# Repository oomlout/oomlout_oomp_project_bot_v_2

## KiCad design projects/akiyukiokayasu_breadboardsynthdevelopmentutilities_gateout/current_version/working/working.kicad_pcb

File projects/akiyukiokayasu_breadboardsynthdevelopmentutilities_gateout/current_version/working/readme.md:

# breadboardsynthdevelopmentutilities
 
## summary 
* id: akiyukiokayasu_breadboardsynthdevelopmentutilities_gateout
* user: akiyukiokayasu
* name: breadboardsynthdevelopmentutilities
* board: gateout
* repo: https://github.com/AkiyukiOkayasu/BreadBoardSynthDevelopmentUtilities
* src_file_repo_kicad_pcb: GateOut/GateOut.kicad_pcb
* src_file_repo_kicad_pcb_link: https://github.com/AkiyukiOkayasu/BreadBoardSynthDevelopmentUtilities/tree/main/GateOut/GateOut.kicad_pcb
* src_file_repo_kicad_sch: GateOut/GateOut.kicad_sch
* src_file_repo_kicad_sch_link: https://github.com/AkiyukiOkayasu/BreadBoardSynthDevelopmentUtilities/tree/main/GateOut/GateOut.kicad_sch

* src_file_repo_sch: 
* src_file_repo_sch_link: https://github.com/AkiyukiOkayasu/BreadBoardSynthDevelopmentUtilities/tree/main/
* full details link: https://github.com/oomlout/oomlout_oomp_project_bot_v_2/tree/main/projects/akiyukiokayasu_breadboardsynthdevelopmentutilities_gateout/current_version/working  

## schematic  
  
[schematic (pdf)](working_schematic.pdf) 

## pcb  

[board (pdf)](working.pdf)  

## working_bom
| Id | Designator | Footprint | Quantity | Designation | Supplier and ref |  | None | 
| --- | --- | --- | --- | --- | --- | --- | --- | 
| 1 | R6,R4 | R_0402_1005Metric_Pad0.72x0.64mm_HandSolder | 2 | 10k |  |  | [''] | 
| 2 | U1 | SOIC-8_3.9x4.9mm_P1.27mm | 1 | LM358 |  |  | [''] | 
| 3 | R5,R3 | R_0402_1005Metric_Pad0.72x0.64mm_HandSolder | 2 | 39k |  |  | [''] | 
| 4 | R7,R8 | R_0402_1005Metric_Pad0.72x0.64mm_HandSolder | 2 | 56k |  |  | [''] | 
| 5 | D1,D2 | LED_0402_1005Metric_Pad0.77x0.64mm_HandSolder | 2 | LED |  |  | [''] | 
| 6 | R9,R1,R2,R10 | R_0402_1005Metric_Pad0.72x0.64mm_HandSolder | 4 | 1k |  |  | [''] | 
| 7 | C1 | C_0402_1005Metric_Pad0.74x0.62mm_HandSolder | 1 | 0.1u |  |  | [''] | 
| 8 | J2,J1 | PinHeader_1x04_P2.54mm_Vertical | 2 | Conn_01x04 |  |  | [''] | 

## bom_schematic
| Ref | Qnty | Value | Cmp name | Footprint | Description | Vendor | DNP | 
| --- | --- | --- | --- | --- | --- | --- | --- | 
| C1 | 1 | 0.1u | C_Small | Capacitor_SMD:C_0402_1005Metric_Pad0.74x0.62mm_HandSolder | Unpolarized capacitor, small symbol |  |  | 
| D1, D2 | 2 | LED | LED | LED_SMD:LED_0402_1005Metric_Pad0.77x0.64mm_HandSolder | Light emitting diode |  |  | 
| J1, J2 | 2 | Conn_01x04 | Conn_01x04 | Connector_PinHeader_2.54mm:PinHeader_1x04_P2.54mm_Vertical | Generic connector, single row, 01x04, script generated (kicad-library-utils/schlib/autogen/connector/) |  |  | 
| R1, R2, R9, R10 | 4 | 1k | R | Resistor_SMD:R_0402_1005Metric_Pad0.72x0.64mm_HandSolder | Resistor |  |  | 
| R3, R5 | 2 | 39k | R | Resistor_SMD:R_0402_1005Metric_Pad0.72x0.64mm_HandSolder | Resistor |  |  | 
| R4, R6 | 2 | 10k | R | Resistor_SMD:R_0402_1005Metric_Pad0.72x0.64mm_HandSolder | Resistor |  |  | 
| R7, R8 | 2 | 56k | R | Resistor_SMD:R_0402_1005Metric_Pad0.72x0.64mm_HandSolder | Resistor |  |  | 
| U1 | 1 | LM358 | LM358 | Package_SO:SOIC-8_3.9x4.9mm_P1.27mm | Low-Power, Dual Operational Amplifiers, DIP-8/SOIC-8/TO-99-8 |  |  |

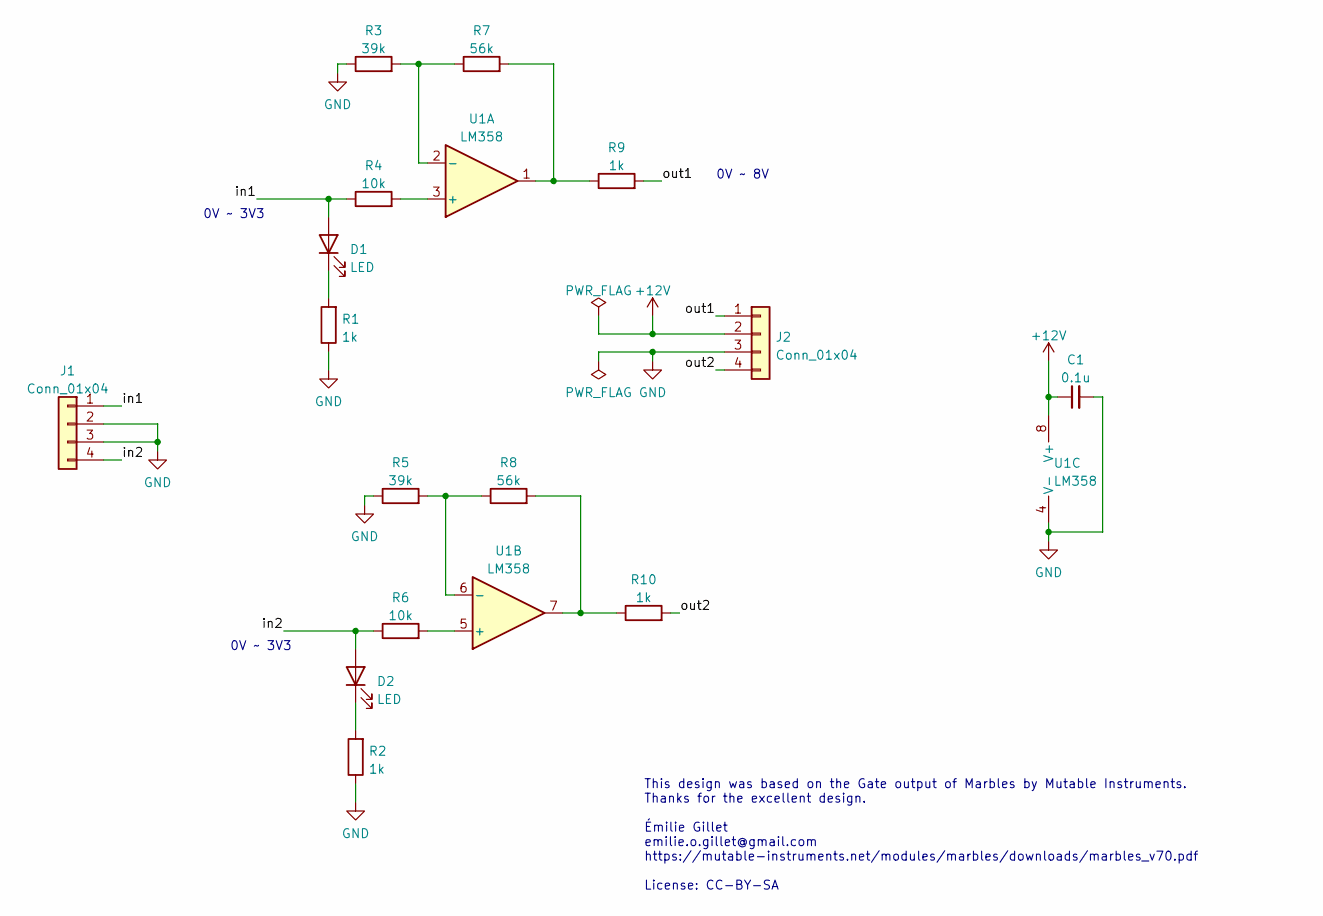
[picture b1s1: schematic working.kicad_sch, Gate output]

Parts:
C1: 0.1u; C_0402_1005Metric_Pad0.74x0.62mm_HandSolder
D1, D2: LED; LED_0402_1005Metric_Pad0.77x0.64mm_HandSolder
J1, J2: Conn_01x04; PinHeader_1x04_P2.54mm_Vertical
R1, R2, R9, R10: 1k; R_0402_1005Metric_Pad0.72x0.64mm_HandSolder
R3, R5: 39k; R_0402_1005Metric_Pad0.72x0.64mm_HandSolder
R4, R6: 10k; R_0402_1005Metric_Pad0.72x0.64mm_HandSolder
R7, R8: 56k; R_0402_1005Metric_Pad0.72x0.64mm_HandSolder
U1: LM358; SOIC-8_3.9x4.9mm_P1.27mm

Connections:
+12V: C1.1, J2.2, U1.8 (V+)
/in1: D1.2 (A), J1.1, R4.1
/in2: D2.2 (A), J1.4, R6.1
/out1: J2.1, R9.2
/out2: J2.4, R10.2
GND: C1.2, J1.2, J1.3, J2.3, R1.1, R2.1, R3.1, R5.1, U1.4 (V-)
unnamed: D1.1 (K), R1.2
unnamed: D2.1 (K), R2.2
unnamed: R3.2, R7.1, U1.2 (-)
unnamed: R4.2, U1.3 (+)
unnamed: R5.2, R8.1, U1.6 (-)
unnamed: R6.2, U1.5 (+)
unnamed: R7.2, R9.1, U1.1
unnamed: R8.2, R10.1, U1.7

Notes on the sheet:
0V ~ 3V3
This design was based on the Gate output of Marbles by Mutable Instruments. Thanks for the excellent design. Émilie Gillet emilie.o.gillet@gmail.com https://mutable-instruments.net/modules/marbles/downloads/marbles_v70.pdf License: CC-BY-SA
0V ~ 8V

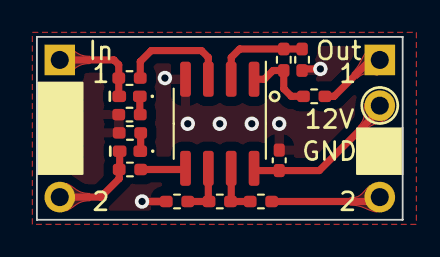
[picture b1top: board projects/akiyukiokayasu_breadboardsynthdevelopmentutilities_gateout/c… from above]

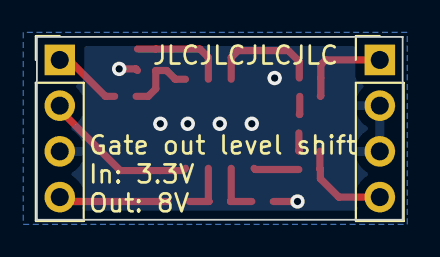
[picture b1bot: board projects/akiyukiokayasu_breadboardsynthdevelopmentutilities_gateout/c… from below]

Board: 2 copper layers, 20.3 x 10.2 mm, 16 parts (2 on the bottom side), 14 nets.

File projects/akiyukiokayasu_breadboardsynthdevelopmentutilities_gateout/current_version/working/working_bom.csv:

"Id";"Designator";"Footprint";"Quantity";"Designation";"Supplier and ref";
1;"R6,R4";"R_0402_1005Metric_Pad0.72x0.64mm_HandSolder";2;"10k";;;
2;"U1";"SOIC-8_3.9x4.9mm_P1.27mm";1;"LM358";;;
3;"R5,R3";"R_0402_1005Metric_Pad0.72x0.64mm_HandSolder";2;"39k";;;
4;"R7,R8";"R_0402_1005Metric_Pad0.72x0.64mm_HandSolder";2;"56k";;;
5;"D1,D2";"LED_0402_1005Metric_Pad0.77x0.64mm_HandSolder";2;"LED";;;
6;"R9,R1,R2,R10";"R_0402_1005Metric_Pad0.72x0.64mm_HandSolder";4;"1k";;;
7;"C1";"C_0402_1005Metric_Pad0.74x0.62mm_HandSolder";1;"0.1u";;;
8;"J2,J1";"PinHeader_1x04_P2.54mm_Vertical";2;"Conn_01x04";;;

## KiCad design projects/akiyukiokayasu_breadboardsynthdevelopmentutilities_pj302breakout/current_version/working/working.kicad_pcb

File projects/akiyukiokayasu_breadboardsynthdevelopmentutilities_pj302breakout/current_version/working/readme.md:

# breadboardsynthdevelopmentutilities
 
## summary 
* id: akiyukiokayasu_breadboardsynthdevelopmentutilities_pj302breakout
* user: akiyukiokayasu
* name: breadboardsynthdevelopmentutilities
* board: pj302breakout
* repo: https://github.com/AkiyukiOkayasu/BreadBoardSynthDevelopmentUtilities
* src_file_repo_kicad_pcb: PJ302Breakout/PJ302Breakout.kicad_pcb
* src_file_repo_kicad_pcb_link: https://github.com/AkiyukiOkayasu/BreadBoardSynthDevelopmentUtilities/tree/main/PJ302Breakout/PJ302Breakout.kicad_pcb
* src_file_repo_kicad_sch: PJ302Breakout/PJ302Breakout.kicad_sch
* src_file_repo_kicad_sch_link: https://github.com/AkiyukiOkayasu/BreadBoardSynthDevelopmentUtilities/tree/main/PJ302Breakout/PJ302Breakout.kicad_sch

* src_file_repo_sch: 
* src_file_repo_sch_link: https://github.com/AkiyukiOkayasu/BreadBoardSynthDevelopmentUtilities/tree/main/
* full details link: https://github.com/oomlout/oomlout_oomp_project_bot_v_2/tree/main/projects/akiyukiokayasu_breadboardsynthdevelopmentutilities_pj302breakout/current_version/working  

## schematic  
  
[schematic (pdf)](working_schematic.pdf) 

## pcb  

[board (pdf)](working.pdf)  

## working_bom
| Id | Designator | Footprint | Quantity | Designation | Supplier and ref |  | None | 
| --- | --- | --- | --- | --- | --- | --- | --- | 
| 1 | J1 | PJ302M | 1 | PJ302M |  |  | [''] | 
| 2 | J3 | PinHeader_1x02_P2.54mm_Vertical | 1 | Conn_01x02 |  |  | [''] | 
| 3 | J2 | PinHeader_1x04_P2.54mm_Vertical | 1 | Conn_01x04 |  |  | [''] | 

## bom_schematic
| Ref | Qnty | Value | Cmp name | Footprint | Description | Vendor | DNP | 
| --- | --- | --- | --- | --- | --- | --- | --- | 
| J1 | 1 | PJ302M | PJ302M | Akiyuki_Footprint:PJ302M | 2-pin audio jack receptable (mono/TS connector) with switching contact |  |  | 
| J2 | 1 | Conn_01x04 | Conn_01x04 | Connector_PinHeader_2.54mm:PinHeader_1x04_P2.54mm_Vertical | Generic connector, single row, 01x04, script generated (kicad-library-utils/schlib/autogen/connector/) |  |  | 
| J3 | 1 | Conn_01x02 | Conn_01x02 | Connector_PinHeader_2.54mm:PinHeader_1x02_P2.54mm_Vertical | Generic connector, single row, 01x02, script generated (kicad-library-utils/schlib/autogen/connector/) |  |  |

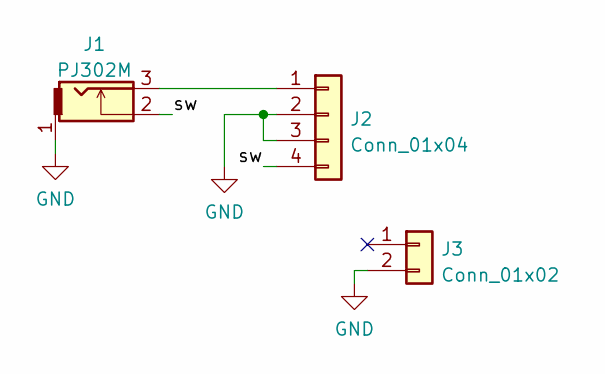
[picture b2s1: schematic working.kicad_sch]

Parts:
J1: PJ302M
J2: Conn_01x04; PinHeader_1x04_P2.54mm_Vertical
J3: Conn_01x02; PinHeader_1x02_P2.54mm_Vertical

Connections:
/sw: J1.2, J2.4
GND: J1.1, J2.2, J2.3, J3.2
unnamed: J1.3, J2.1

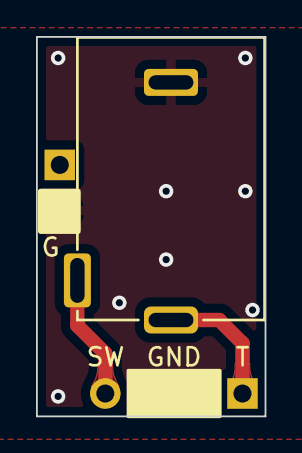
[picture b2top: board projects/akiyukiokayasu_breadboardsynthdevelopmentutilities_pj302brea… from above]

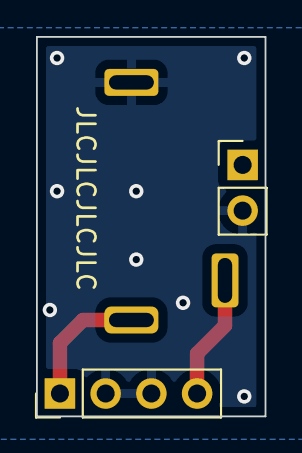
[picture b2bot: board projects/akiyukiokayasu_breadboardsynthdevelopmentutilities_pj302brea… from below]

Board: 2 copper layers, 12.7 x 21.1 mm, 3 parts (2 on the bottom side), 3 nets.

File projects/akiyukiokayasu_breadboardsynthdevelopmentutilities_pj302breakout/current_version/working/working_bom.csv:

"Id";"Designator";"Footprint";"Quantity";"Designation";"Supplier and ref";
1;"J1";"PJ302M";1;"PJ302M";;;
2;"J3";"PinHeader_1x02_P2.54mm_Vertical";1;"Conn_01x02";;;
3;"J2";"PinHeader_1x04_P2.54mm_Vertical";1;"Conn_01x04";;;

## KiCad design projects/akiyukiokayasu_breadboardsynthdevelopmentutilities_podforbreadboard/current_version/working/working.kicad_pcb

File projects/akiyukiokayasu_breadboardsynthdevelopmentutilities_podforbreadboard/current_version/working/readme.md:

# breadboardsynthdevelopmentutilities
 
## summary 
* id: akiyukiokayasu_breadboardsynthdevelopmentutilities_podforbreadboard
* user: akiyukiokayasu
* name: breadboardsynthdevelopmentutilities
* board: podforbreadboard
* repo: https://github.com/AkiyukiOkayasu/BreadBoardSynthDevelopmentUtilities
* src_file_repo_kicad_pcb: PodForBreadboard/PodForBreadboard.kicad_pcb
* src_file_repo_kicad_pcb_link: https://github.com/AkiyukiOkayasu/BreadBoardSynthDevelopmentUtilities/tree/main/PodForBreadboard/PodForBreadboard.kicad_pcb
* src_file_repo_kicad_sch: PodForBreadboard/PodForBreadboard.kicad_sch
* src_file_repo_kicad_sch_link: https://github.com/AkiyukiOkayasu/BreadBoardSynthDevelopmentUtilities/tree/main/PodForBreadboard/PodForBreadboard.kicad_sch

* src_file_repo_sch: 
* src_file_repo_sch_link: https://github.com/AkiyukiOkayasu/BreadBoardSynthDevelopmentUtilities/tree/main/
* full details link: https://github.com/oomlout/oomlout_oomp_project_bot_v_2/tree/main/projects/akiyukiokayasu_breadboardsynthdevelopmentutilities_podforbreadboard/current_version/working  

## schematic  
  
[schematic (pdf)](working_schematic.pdf) 

## pcb  

[board (pdf)](working.pdf)  

## working_bom
| Id | Designator | Footprint | Quantity | Designation | Supplier and ref |  | None | 
| --- | --- | --- | --- | --- | --- | --- | --- | 
| 1 | RV1 | ALPS_RK09D117000B | 1 | ALPS_RK09D |  |  | [''] | 
| 2 | J1 | PinHeader_2x02_P2.54mm_Vertical | 1 | Conn_02x02_Odd_Even |  |  | [''] | 
| 3 | J2 | PinHeader_1x04_P2.54mm_Vertical | 1 | Conn_01x04 |  |  | [''] | 

## bom_schematic
| Ref | Qnty | Value | Cmp name | Footprint | Description | Vendor | DNP | 
| --- | --- | --- | --- | --- | --- | --- | --- | 
| J1 | 1 | Conn_02x02_Odd_Even | Conn_02x02_Odd_Even | Connector_PinHeader_2.54mm:PinHeader_2x02_P2.54mm_Vertical | Generic connector, double row, 02x02, odd/even pin numbering scheme (row 1 odd numbers, row 2 even numbers), script generated (kicad-library-utils/schlib/autogen/connector/) |  |  | 
| J2 | 1 | Conn_01x04 | Conn_01x04 | Connector_PinHeader_2.54mm:PinHeader_1x04_P2.54mm_Vertical | Generic connector, single row, 01x04, script generated (kicad-library-utils/schlib/autogen/connector/) |  |  | 
| RV1 | 1 | ALPS_RK09D | ALPS_RK09D | Akiyuki_Footprint:ALPS_RK09D117000B | Pot |  |  |

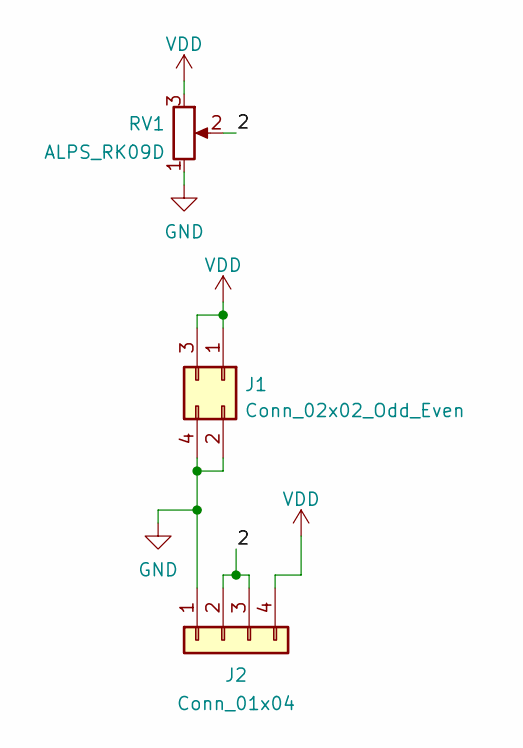
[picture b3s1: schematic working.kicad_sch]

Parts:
J1: Conn_02x02_Odd_Even; PinHeader_2x02_P2.54mm_Vertical
J2: Conn_01x04; PinHeader_1x04_P2.54mm_Vertical
RV1: ALPS_RK09D; ALPS_RK09D117000B

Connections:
/2: J2.2, J2.3, RV1.2
GND: J1.2, J1.4, J2.1, RV1.1
VDD: J1.1, J1.3, J2.4, RV1.3

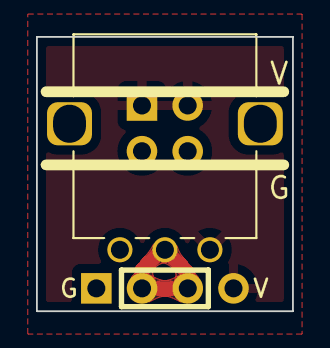
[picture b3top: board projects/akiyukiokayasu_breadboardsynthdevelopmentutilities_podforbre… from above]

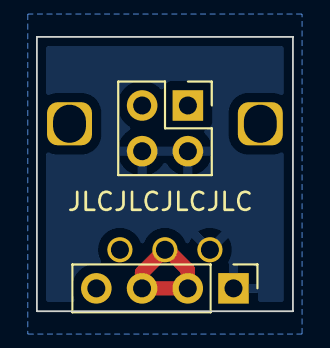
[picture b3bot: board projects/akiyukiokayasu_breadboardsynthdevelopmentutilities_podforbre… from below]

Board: 2 copper layers, 14.2 x 15.2 mm, 3 parts (2 on the bottom side), 3 nets.

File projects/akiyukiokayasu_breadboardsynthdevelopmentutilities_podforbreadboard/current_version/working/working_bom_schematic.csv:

"Source:","C:\gh\oomlout_oomp_project_bot_v_2\projects\akiyukiokayasu_breadboardsynthdevelopmentutilities_podforbreadboard\current_version\working\working.kicad_sch"
"Date:","11/09/2023 22:35:03"
"Tool:","Eeschema 7.0.6"
"Generator:","C:/Program Files/KiCad/7.0/bin/scripting/plugins/bom_csv_grouped_by_value_with_fp.py"
"Component Count:","3"
"Ref","Qnty","Value","Cmp name","Footprint","Description","Vendor","DNP"
"J1","1","Conn_02x02_Odd_Even","Conn_02x02_Odd_Even","Connector_PinHeader_2.54mm:PinHeader_2x02_P2.54mm_Vertical","Generic connector, double row, 02x02, odd/even pin numbering scheme (row 1 odd numbers, row 2 even numbers), script generated (kicad-library-utils/schlib/autogen/connector/)","",""
"J2","1","Conn_01x04","Conn_01x04","Connector_PinHeader_2.54mm:PinHeader_1x04_P2.54mm_Vertical","Generic connector, single row, 01x04, script generated (kicad-library-utils/schlib/autogen/connector/)","",""
"RV1","1","ALPS_RK09D","ALPS_RK09D","Akiyuki_Footprint:ALPS_RK09D117000B","Pot","",""

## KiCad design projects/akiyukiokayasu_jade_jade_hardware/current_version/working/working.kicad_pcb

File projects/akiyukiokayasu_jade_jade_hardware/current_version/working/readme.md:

# jade
 
## summary 
* id: akiyukiokayasu_jade_jade_hardware
* user: akiyukiokayasu
* name: jade
* board: jade_hardware
* repo: https://github.com/AkiyukiOkayasu/jade
* src_file_repo_kicad_pcb: Hardware/jade_hardware.kicad_pcb
* src_file_repo_kicad_pcb_link: https://github.com/AkiyukiOkayasu/jade/tree/main/Hardware/jade_hardware.kicad_pcb
* src_file_repo_kicad_sch: Hardware/jade_hardware.kicad_sch
* src_file_repo_kicad_sch_link: https://github.com/AkiyukiOkayasu/jade/tree/main/Hardware/jade_hardware.kicad_sch

* src_file_repo_sch: 
* src_file_repo_sch_link: https://github.com/AkiyukiOkayasu/jade/tree/main/
* full details link: https://github.com/oomlout/oomlout_oomp_project_bot_v_2/tree/main/projects/akiyukiokayasu_jade_jade_hardware/current_version/working  

## schematic  
  
[schematic (pdf)](working_schematic.pdf) 

## pcb  

[board (pdf)](working.pdf)  

## working_bom
| Id | Designator | Footprint | Quantity | Designation | Supplier and ref |  | None | 
| --- | --- | --- | --- | --- | --- | --- | --- | 
| 1 | C1 | C_0805_2012Metric_Pad1.18x1.45mm_HandSolder | 1 | 10u |  |  | [''] | 
| 2 | C2 | C_0603_1608Metric_Pad1.08x0.95mm_HandSolder | 1 | 0.1u |  |  | [''] | 
| 3 | D1,D2,D3,D4 | D_SOD-123 | 4 | 1N4148W |  |  | [''] | 
| 4 | D5 | D_SOD-123 | 1 | 1N5819HW |  |  | [''] | 
| 5 | J1,J2,J3,J4,J7,J8 | PJ302M | 6 | PJ302M |  |  | [''] | 
| 6 | J5 | PinHeader_2x05_P2.54mm_Horizontal | 1 | Conn_02x05_Odd_Even |  |  | [''] | 
| 7 | J6 | PinHeader_2x03_P2.54mm_Horizontal | 1 | Conn_02x03_Odd_Even |  |  | [''] | 
| 8 | R1,R3,R4,R5,R6,R8,R2,R7 | R_0603_1608Metric_Pad0.98x0.95mm_HandSolder | 8 | 100k |  |  | [''] | 
| 9 | R9,R10 | R_0603_1608Metric_Pad0.98x0.95mm_HandSolder | 2 | 39k |  |  | [''] | 
| 10 | R13,R14 | R_0603_1608Metric_Pad0.98x0.95mm_HandSolder | 2 | 56k |  |  | [''] | 
| 11 | R15,R16 | R_0603_1608Metric_Pad0.98x0.95mm_HandSolder | 2 | 1k |  |  | [''] | 
| 12 | U2 | SOP-8_3.9x4.9mm_P1.27mm | 1 | LM358 |  |  | [''] | 
| 13 | Q4,Q3,Q2,Q1 | SOT-23 | 4 | MMBT3904 |  |  | [''] | 
| 14 | U1 | Seeeduino_XIAO_NonBottomPad | 1 | SeeeduinoXIAO |  |  | [''] | 
| 15 | R12,R11 | R_0603_1608Metric_Pad0.98x0.95mm_HandSolder | 2 | 47k |  |  | [''] | 

## bom_schematic
| Ref | Qnty | Value | Cmp name | Footprint | Description | Vendor | DNP | 
| --- | --- | --- | --- | --- | --- | --- | --- | 
| C1, C2 | 2 | 10u | C_Small | Capacitor_SMD:C_0805_2012Metric_Pad1.18x1.45mm_HandSolder | Unpolarized capacitor, small symbol |  |  | 
| C3, C4 | 2 | 0.1u | C_Small | Capacitor_SMD:C_0402_1005Metric_Pad0.74x0.62mm_HandSolder | Unpolarized capacitor, small symbol |  |  | 
| D1, D2, D3, D4 | 4 | 1N4148W | D_Small | Diode_SMD:D_SOD-123 | Diode, small symbol |  |  | 
| D5 | 1 | 1N5819HW | D_Small | Diode_SMD:D_SOD-123 | Diode, small symbol |  |  | 
| J1, J2, J3, J4, J6, J7 | 6 | PJ302M | PJ302M | Akiyuki_Footprint:PJ302M | 2-pin audio jack receptable (mono/TS connector) with switching contact |  |  | 
| J5 | 1 | Conn_02x05_Odd_Even | Conn_02x05_Odd_Even | Connector_PinHeader_2.54mm:PinHeader_2x05_P2.54mm_Horizontal | Generic connector, double row, 02x05, odd/even pin numbering scheme (row 1 odd numbers, row 2 even numbers), script generated (kicad-library-utils/schlib/autogen/connector/) |  |  | 
| J8 | 1 | monome ii | Conn_02x03_Odd_Even | Connector_PinHeader_2.54mm:PinHeader_2x03_P2.54mm_Horizontal | Generic connector, double row, 02x03, odd/even pin numbering scheme (row 1 odd numbers, row 2 even numbers), script generated (kicad-library-utils/schlib/autogen/connector/) |  |  | 
| Q1 | 1 | DTC114E | DTC114E |  | Digital NPN Transistor, 10k/10k, SOT-23 |  |  | 
| R1, R2, R3, R4 | 4 | 100k | R_Small | Resistor_SMD:R_0402_1005Metric_Pad0.72x0.64mm_HandSolder | Resistor, small symbol |  |  | 
| R5, R6 | 2 | 47k | R_Small | Resistor_SMD:R_0402_1005Metric_Pad0.72x0.64mm_HandSolder | Resistor, small symbol |  |  | 
| R7, R8 | 2 | 2k2 | R_Small | Resistor_SMD:R_0402_1005Metric_Pad0.72x0.64mm_HandSolder | Resistor, small symbol |  |  | 
| SW1 | 1 | SW_DIP_x02 | SW_DIP_x02 | Akiyuki_Footprint:OTAX_KHS_2 | 2x DIP Switch, Single Pole Single Throw (SPST) switch, small symbol |  |  | 
| U1 | 1 | TLP293-4 | TLP291-4 | Package_SO:SOIC-16_4.55x10.3mm_P1.27mm | Quad DC Optocoupler, Vce 80V, CTR 50-100%, SOP16 |  |  | 
| U2 | 1 | SeeeduinoXIAO | SeeeduinoXIAO_NonBottomPad | Akiyuki_Footprint:Seeeduino_XIAO_NonBottomPad |  |  |  | 
| U3 | 1 | MIC39100 | MIC39100 | Package_TO_SOT_SMD:SOT-223-3_TabPin2 | Linear Voltage Regulator IC 1 Output 1A SOT-223-3 |  |  | 
| U4, U5 | 2 | TLP291 | TLP291 | Package_SO:SOIC-4_4.55x2.6mm_P1.27mm | DC Optocoupler, Vce 80V, CTR 50-100%, SOP4 |  |  | 
| U6 | 1 | ADuM1250 | ADuM1250 | Package_SO:SOIC-8_3.9x4.9mm_P1.27mm | I2C isolator |  |  |

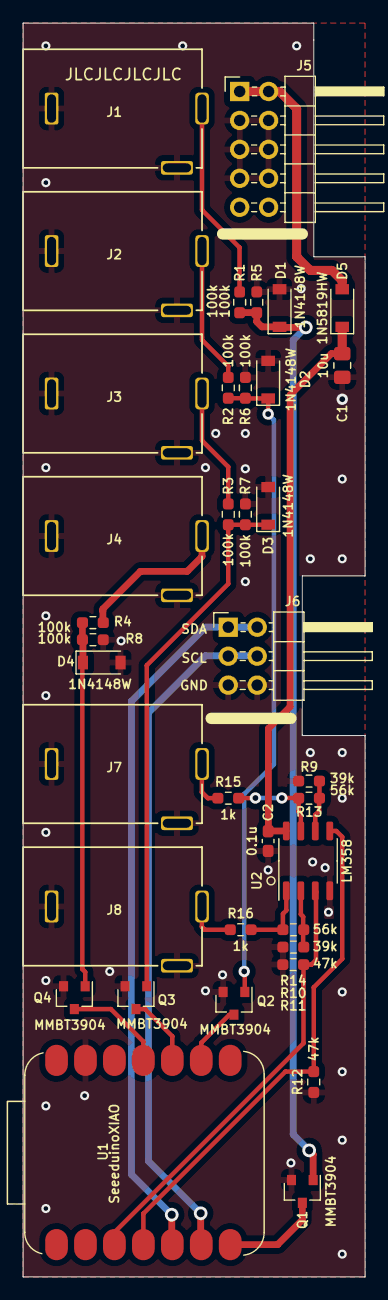
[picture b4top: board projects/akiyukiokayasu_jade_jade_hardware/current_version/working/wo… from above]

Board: 2 copper layers, 30.0 x 110.0 mm, 37 parts (0 on the bottom side), 25 nets.

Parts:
C1: 10u; C_0805_2012Metric_Pad1.18x1.45mm_HandSolder
C2: 0.1u; C_0603_1608Metric_Pad1.08x0.95mm_HandSolder
D1, D2, D3, D4: 1N4148W; D_SOD-123
D5: 1N5819HW; D_SOD-123
J1, J2, J3, J4, J7, J8: PJ302M
J5: Conn_02x05_Odd_Even; PinHeader_2x05_P2.54mm_Horizontal
J6: Conn_02x03_Odd_Even; PinHeader_2x03_P2.54mm_Horizontal
Q1, Q2, Q3, Q4: MMBT3904; SOT-23
R1, R2, R3, R4, R5, R6, R7, R8: 100k; R_0603_1608Metric_Pad0.98x0.95mm_HandSolder
R9, R10: 39k; R_0603_1608Metric_Pad0.98x0.95mm_HandSolder
R11, R12: 47k; R_0603_1608Metric_Pad0.98x0.95mm_HandSolder
R13, R14: 56k; R_0603_1608Metric_Pad0.98x0.95mm_HandSolder
R15, R16: 1k; R_0603_1608Metric_Pad0.98x0.95mm_HandSolder
U1: SeeeduinoXIAO; Seeeduino_XIAO_NonBottomPad
U2: LM358; SOP-8_3.9x4.9mm_P1.27mm

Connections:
+12V: C1.1, C2.1, D5.1, U2.8
/CLOCK_OUT: R11.2, U1.3, U2.3
/GATE_IN1: Q1.3, U1.7
/GATE_IN2: Q2.3, U1.9
/GATE_IN3: Q3.3, U1.10
/GATE_IN4: Q4.3, U1.11
/GATE_OUT: R12.2, U1.4, U2.5
/SCL: J6.3, J6.4, U1.6
/SDA: J6.1, J6.2, U1.5
GND: C1.2, C2.2, D1.2, D2.2, D3.2, D4.2, J1.1, J1.2, J2.1, J2.2, J3.1, J3.2, J4.1, J4.2, J5.3, J5.4, J5.5, J5.6, J5.7, J5.8, J6.5, J6.6, J7.1, J7.2, J8.1, J8.2, Q1.2, Q2.2, Q3.2, Q4.2, R5.1, R6.1, R7.1, R8.1, R9.2, R10.2, R11.1, R12.1, U1.13, U2.4
unnamed: D1.1, Q1.1, R1.1, R5.2
unnamed: D2.1, Q2.1, R2.1, R6.2
unnamed: D3.1, Q3.1, R3.1, R7.2
unnamed: D4.1, Q4.1, R4.1, R8.2
unnamed: D5.2, J5.1, J5.2
unnamed: J1.3, R1.2
unnamed: J2.3, R2.2
unnamed: J3.3, R3.2
unnamed: J4.3, R4.2
unnamed: J7.3, R15.1
unnamed: J8.3, R16.1
unnamed: R10.1, R14.2, U2.2
unnamed: R13.1, R15.2, U2.7
unnamed: R9.1, R13.2, U2.6
unnamed: R14.1, R16.2, U2.1

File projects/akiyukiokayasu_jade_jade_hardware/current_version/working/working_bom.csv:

"Id";"Designator";"Footprint";"Quantity";"Designation";"Supplier and ref";
1;"C1";"C_0805_2012Metric_Pad1.18x1.45mm_HandSolder";1;"10u";;;
2;"C2";"C_0603_1608Metric_Pad1.08x0.95mm_HandSolder";1;"0.1u";;;
3;"D1,D2,D3,D4";"D_SOD-123";4;"1N4148W";;;
4;"D5";"D_SOD-123";1;"1N5819HW";;;
5;"J1,J2,J3,J4,J7,J8";"PJ302M";6;"PJ302M";;;
6;"J5";"PinHeader_2x05_P2.54mm_Horizontal";1;"Conn_02x05_Odd_Even";;;
7;"J6";"PinHeader_2x03_P2.54mm_Horizontal";1;"Conn_02x03_Odd_Even";;;
8;"R1,R3,R4,R5,R6,R8,R2,R7";"R_0603_1608Metric_Pad0.98x0.95mm_HandSolder";8;"100k";;;
9;"R9,R10";"R_0603_1608Metric_Pad0.98x0.95mm_HandSolder";2;"39k";;;
10;"R13,R14";"R_0603_1608Metric_Pad0.98x0.95mm_HandSolder";2;"56k";;;
11;"R15,R16";"R_0603_1608Metric_Pad0.98x0.95mm_HandSolder";2;"1k";;;
12;"U2";"SOP-8_3.9x4.9mm_P1.27mm";1;"LM358";;;
13;"Q4,Q3,Q2,Q1";"SOT-23";4;"MMBT3904";;;
14;"U1";"Seeeduino_XIAO_NonBottomPad";1;"SeeeduinoXIAO";;;
15;"R12,R11";"R_0603_1608Metric_Pad0.98x0.95mm_HandSolder";2;"47k";;;

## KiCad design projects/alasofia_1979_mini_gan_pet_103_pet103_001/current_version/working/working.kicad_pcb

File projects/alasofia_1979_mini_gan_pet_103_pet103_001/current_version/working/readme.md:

# 1979_mini_gan_pet_103
 
## summary 
* id: alasofia_1979_mini_gan_pet_103_pet103_001
* user: alasofia
* name: 1979_mini_gan_pet_103
* board: pet103_001
* repo: https://github.com/Alasofia/1979-MINI-GAN-PET-103
* src_file_repo_kicad_pcb: KiCad/PET103_001/PET103_001.kicad_pcb
* src_file_repo_kicad_pcb_link: https://github.com/Alasofia/1979-MINI-GAN-PET-103/tree/main/KiCad/PET103_001/PET103_001.kicad_pcb

* src_file_repo_sch: KiCad/PET103_001/PET103_001.sch
* src_file_repo_sch_link: https://github.com/Alasofia/1979-MINI-GAN-PET-103/tree/main/KiCad/PET103_001/PET103_001.sch
* full details link: https://github.com/oomlout/oomlout_oomp_project_bot_v_2/tree/main/projects/alasofia_1979_mini_gan_pet_103_pet103_001/current_version/working  

## schematic  
  
[schematic (pdf)](working_schematic.pdf) 

## pcb  

[board (pdf)](working.pdf)  

## working_bom
| Id | Designator | Footprint | Quantity | Designation | Supplier and ref |  | None | 
| --- | --- | --- | --- | --- | --- | --- | --- | 
| 1 | C1 | C_Disc_D4.7mm_W2.5mm_P5.00mm | 1 | 150PF |  |  | [''] | 
| 2 | C2 | CP_Radial_D5.0mm_P2.50mm | 1 | 470ÂµF |  |  | [''] | 
| 3 | C3 | C_Disc_D4.7mm_W2.5mm_P5.00mm | 1 | 683 |  |  | [''] | 
| 4 | C4 | CP_Radial_D5.0mm_P2.50mm | 1 | 220ÂµF |  |  | [''] | 
| 5 | C5 | CP_Radial_D5.0mm_P2.50mm | 1 | 4.7ÂµF |  |  | [''] | 
| 6 | C6,C7 | CP_Radial_D5.0mm_P2.50mm | 2 | 47ÂµF |  |  | [''] | 
| 7 | C8 | C_Disc_D4.7mm_W2.5mm_P5.00mm | 1 | 104 |  |  | [''] | 
| 8 | C9,C10 | CP_Radial_D5.0mm_P2.50mm | 2 | 100ÂµF |  |  | [''] | 
| 9 | C11,C13,C15,C16,C17 | CP_Radial_D5.0mm_P2.50mm | 5 | 1ÂµF |  |  | [''] | 
| 10 | C12 | C_Disc_D4.7mm_W2.5mm_P5.00mm | 1 | 223 |  |  | [''] | 
| 11 | C14 | C_Disc_D4.7mm_W2.5mm_P5.00mm | 1 | 333 |  |  | [''] | 
| 12 | Q1 | TO-92_Inline | 1 | 2SC1815 |  |  | [''] | 
| 13 | R1 | R_Axial_DIN0207_L6.3mm_D2.5mm_P10.16mm_Horizontal | 1 | 51Î© |  |  | [''] | 
| 14 | R2 | R_Axial_DIN0207_L6.3mm_D2.5mm_P10.16mm_Horizontal | 1 | 100Î© |  |  | [''] | 
| 15 | R3,R7,R10 | R_Axial_DIN0207_L6.3mm_D2.5mm_P10.16mm_Horizontal | 3 | 4.7K |  |  | [''] | 
| 16 | R4 | R_Axial_DIN0207_L6.3mm_D2.5mm_P10.16mm_Horizontal | 1 | 1M |  |  | [''] | 
| 17 | R5 | R_Axial_DIN0207_L6.3mm_D2.5mm_P10.16mm_Horizontal | 1 | 100K |  |  | [''] | 
| 18 | R6,R8 | R_Axial_DIN0207_L6.3mm_D2.5mm_P10.16mm_Horizontal | 2 | 1K |  |  | [''] | 
| 19 | R9,R11 | R_Axial_DIN0207_L6.3mm_D2.5mm_P10.16mm_Horizontal | 2 | 10K |  |  | [''] | 
| 20 | R12 | R_Axial_DIN0207_L6.3mm_D2.5mm_P10.16mm_Horizontal | 1 | 18K |  |  | [''] | 
| 21 | R13 | Potentiometer_Bourns_3266W_Vertical | 1 | 5K |  |  | [''] | 
| 22 | U1 | DIP-8_W7.62mm_LongPads | 1 | LA6458 |  |  | [''] | 
| 23 | U2 | SIP9_Housing_BigPads | 1 | LA4140 |  |  | [''] | 

## bom_schematic
no data

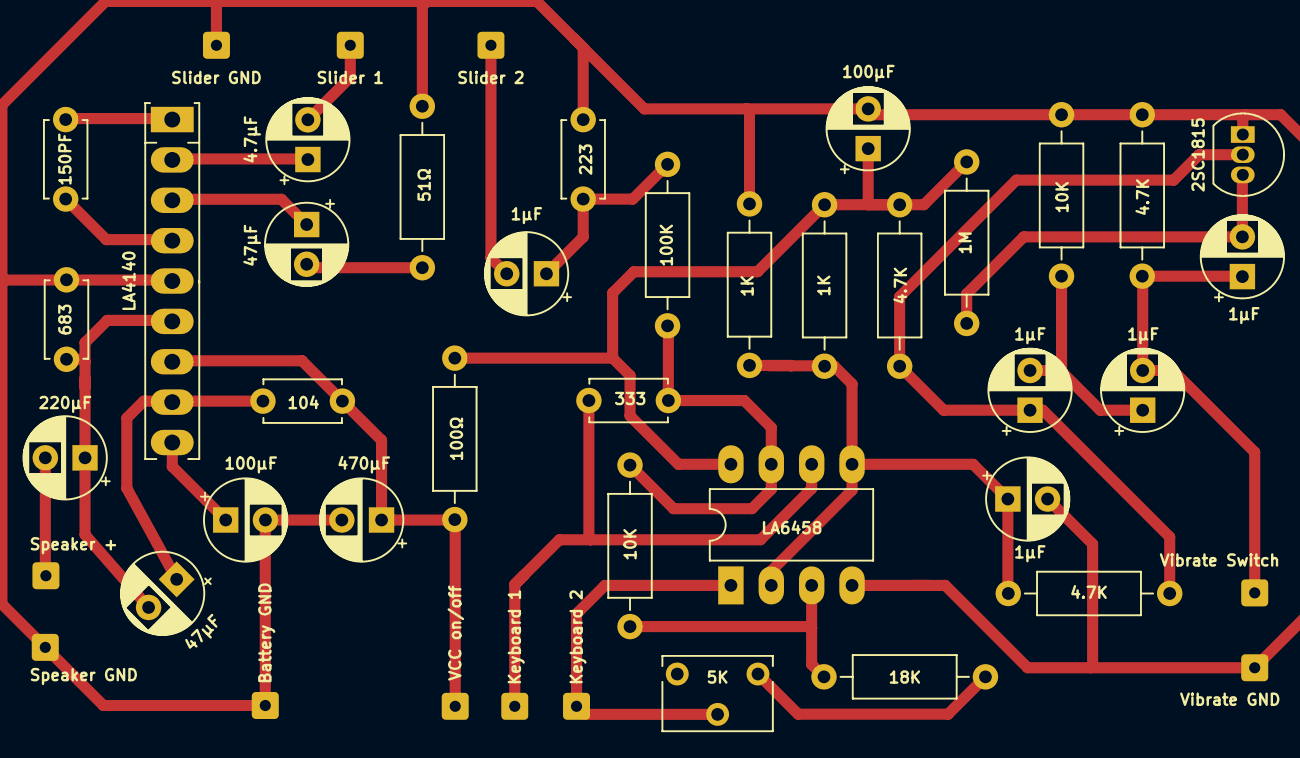
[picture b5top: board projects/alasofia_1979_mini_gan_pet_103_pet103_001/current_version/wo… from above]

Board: 2 copper layers, 44 parts (0 on the bottom side), 25 nets.

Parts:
C1: 150PF; C_Disc_D4.7mm_W2.5mm_P5.00mm
C2: 470µF; CP_Radial_D5.0mm_P2.50mm
C3: 683; C_Disc_D4.7mm_W2.5mm_P5.00mm
C4: 220µF; CP_Radial_D5.0mm_P2.50mm
C5: 4.7µF; CP_Radial_D5.0mm_P2.50mm
C6, C7: 47µF; CP_Radial_D5.0mm_P2.50mm
C8: 104; C_Disc_D4.7mm_W2.5mm_P5.00mm
C9, C10: 100µF; CP_Radial_D5.0mm_P2.50mm
C11, C13, C15, C16, C17: 1µF; CP_Radial_D5.0mm_P2.50mm
C12: 223; C_Disc_D4.7mm_W2.5mm_P5.00mm
C14: 333; C_Disc_D4.7mm_W2.5mm_P5.00mm
J1: Battery GND; SolderWire-0.15sqmm_1x01_D0.5mm_OD1.5mm
J2: Speaker GND; SolderWire-0.15sqmm_1x01_D0.5mm_OD1.5mm
J3: Slider GND; SolderWire-0.15sqmm_1x01_D0.5mm_OD1.5mm
J4: Vibrate GND; SolderWire-0.15sqmm_1x01_D0.5mm_OD1.5mm
J5: VCC on/off; SolderWire-0.15sqmm_1x01_D0.5mm_OD1.5mm
J6: Speaker +; SolderWire-0.15sqmm_1x01_D0.5mm_OD1.5mm
J7: Slider 1; SolderWire-0.15sqmm_1x01_D0.5mm_OD1.5mm
J8: Slider 2; SolderWire-0.15sqmm_1x01_D0.5mm_OD1.5mm
J9: Keyboard 1; SolderWire-0.15sqmm_1x01_D0.5mm_OD1.5mm
J10: Keyboard 2; SolderWire-0.15sqmm_1x01_D0.5mm_OD1.5mm
J11: Vibrate Switch; SolderWire-0.15sqmm_1x01_D0.5mm_OD1.5mm
Q1: 2SC1815; TO-92_Inline
R1: 51Ω; R_Axial_DIN0207_L6.3mm_D2.5mm_P10.16mm_Horizontal
R2: 100Ω; R_Axial_DIN0207_L6.3mm_D2.5mm_P10.16mm_Horizontal
R3, R7, R10: 4.7K; R_Axial_DIN0207_L6.3mm_D2.5mm_P10.16mm_Horizontal
R4: 1M; R_Axial_DIN0207_L6.3mm_D2.5mm_P10.16mm_Horizontal
R5: 100K; R_Axial_DIN0207_L6.3mm_D2.5mm_P10.16mm_Horizontal
R6, R8: 1K; R_Axial_DIN0207_L6.3mm_D2.5mm_P10.16mm_Horizontal
R9, R11: 10K; R_Axial_DIN0207_L6.3mm_D2.5mm_P10.16mm_Horizontal
R12: 18K; R_Axial_DIN0207_L6.3mm_D2.5mm_P10.16mm_Horizontal
R13: 5K; Potentiometer_Bourns_3266W_Vertical
U1: LA6458; DIP-8_W7.62mm_LongPads
U2: LA4140; SIP9_Housing_BigPads

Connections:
G: C11.2, J8.1
GND: C2.2, C3.1, C9.2, C10.2, C12.2, C16.2, J1.1, J2.1, J3.1, J4.1, Q1.1, R1.2, R7.2, R8.1, R9.2, U1.4, U2.5
unnamed: C1.1, U2.1
unnamed: C1.2, U2.4
unnamed: C3.2, C4.1, C7.2, U2.6
unnamed: C5.1, U2.2
unnamed: C6.1, U2.3
unnamed: C6.2, R1.1
unnamed: C7.1, C8.2, U2.8
unnamed: C9.1, U2.9
unnamed: C10.1, R2.1, R3.2, R4.2, R6.2, U1.8
unnamed: C11.1, C12.1, R5.1
unnamed: C13.2, Q1.3, R4.1
unnamed: C14.1, R5.2, R11.2, U1.7
unnamed: C15.1, C17.2, R9.1
unnamed: C16.1, R6.1, R8.2, R10.2, U1.2, U1.5
unnamed: C17.1, Q1.2, R3.1, R10.1
unnamed: R11.1, R12.2, U1.3
unnamed: R12.1, R13.1
O: C5.2, J7.1
P: J10.1, R13.2, U1.1
V: C13.1, C15.2, J11.1, R7.1
VCC: C2.1, C8.1, J5.1, R2.2, U2.7
W: C4.2, J6.1
Y: C14.2, J9.1, U1.6
